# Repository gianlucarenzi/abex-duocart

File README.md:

Atari DUO Cart for ABEX
=====================

This is a Atari Duo Cart board, designed for the Atari PBI & ECI Bus EXtender
or ABEX for short.

This Atari DUO Cart is a derivated work of the famous Uno-Cart Project

Rendered Images
===============
# Front
# Back
# Overall

Hardware License
================
Copyright (C) 2018/2019 Gianluca Renzi <gianlucarenzi@eurek.it> <icjtqr@gmail.com>

The hardware of this project is released as free/open hardware under the
Creative Commons Attribution Share-Alike license. See `LICENSE.hw` for details.

Firmware License
================
Copyright (C) 2019 Gianluca Renzi <icjtqr@gmail.com>

The microcontroller firmware of this project is released as free software,
under the terms of the GNU General Public License v3, or later.  See
`LICENSE.sw` for details.

Software License
================
The host software (amigafloppy tool) is released as free software, under the
terms of the GNU General Public License v3, or later. See `LICENSE.sw` or licence.txt for
details.

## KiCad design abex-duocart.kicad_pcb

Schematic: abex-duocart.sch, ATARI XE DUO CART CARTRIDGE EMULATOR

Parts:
C30: 100n; C_1206_HandSoldering
FT232RPi.1: CONN_01X03; Pin_Header_Straight_1x03
JP1: CONN_01X02; Pin_Header_Straight_1x02
JP2: CONN_01X04; Pin_Header_Angled_1x04
P1: 0877159106; BUS_PCIexpress_64pin
P2, P3, P4, P5: CONN_01X01; MountingHole
R1: 0; R_1206_HandSoldering
R6: 100K; R_1206_HandSoldering
SW2: SW_Push; SW_SPST_FSMSM_3D

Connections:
GND: C30.1, FT232RPi.1.1, JP1.2, JP2.1, P1.A1, P1.A5, P1.A9, P1.A13, P1.A17, P1.A21, P1.A25, P1.A29, P1.A32, P1.B17, P1.B21, P1.B25, R1.2, SW2.1; also elsewhere on the board
SWDCLK: JP2.3, P1.B29; also elsewhere on the board
SWDIO: JP2.2, P1.B27; also elsewhere on the board
SWDRST: C30.2, JP1.1, P1.B31, R6.1, SW2.2; also elsewhere on the board
UART_RX: FT232RPi.1.2; also elsewhere on the board
UART_TX: FT232RPi.1.3; also elsewhere on the board
VCC_3V3: JP2.4, P1.A3, P1.A7, P1.A11, P1.A15, P1.A19, P1.A23, P1.A27, P1.B19, P1.B23, R6.2; also elsewhere on the board
mA0: P1.B32; also elsewhere on the board
mA1: P1.B30; also elsewhere on the board
mA2: P1.B28; also elsewhere on the board
mA3: P1.B26; also elsewhere on the board
mA4: P1.B24; also elsewhere on the board
mA5: P1.B22; also elsewhere on the board
mA6: P1.B20; also elsewhere on the board
mA7: P1.B18; also elsewhere on the board
mA8: P1.B16; also elsewhere on the board
mA9: P1.B14; also elsewhere on the board
mA10: P1.B12; also elsewhere on the board
mA11: P1.B10; also elsewhere on the board
mA12: P1.B8; also elsewhere on the board
mA13: P1.B6; also elsewhere on the board
mA14: P1.B4; also elsewhere on the board
mA15: P1.B2; also elsewhere on the board
mAUDIO: P1.A6, R1.1
mD0: P1.B15; also elsewhere on the board
mD1: P1.B13; also elsewhere on the board
mD2: P1.B11; also elsewhere on the board
mD3: P1.B9; also elsewhere on the board
mD4: P1.B7; also elsewhere on the board
mD5: P1.B5; also elsewhere on the board
mD6: P1.B3; also elsewhere on the board
mD7: P1.B1; also elsewhere on the board
mPHI2: P1.A4; also elsewhere on the board
mR/~W: P1.A10; also elsewhere on the board
mRD4: P1.A24; also elsewhere on the board
mRD5: P1.A28; also elsewhere on the board
~mCCTL: P1.A30; also elsewhere on the board
~mREF: P1.A8; also elsewhere on the board
~mRST: P1.A2; also elsewhere on the board
~mS4: P1.A22; also elsewhere on the board
~mS5: P1.A26; also elsewhere on the board

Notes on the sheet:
DEBUG/PROGRAMMING SECTION MEMORY
MOUNTING HOLES
RESET BUTTON MEM
DNP
ABEX PCI EXPRESS CARD CONNECTOR 64 PIN
A31 is +5VDC. Unused here

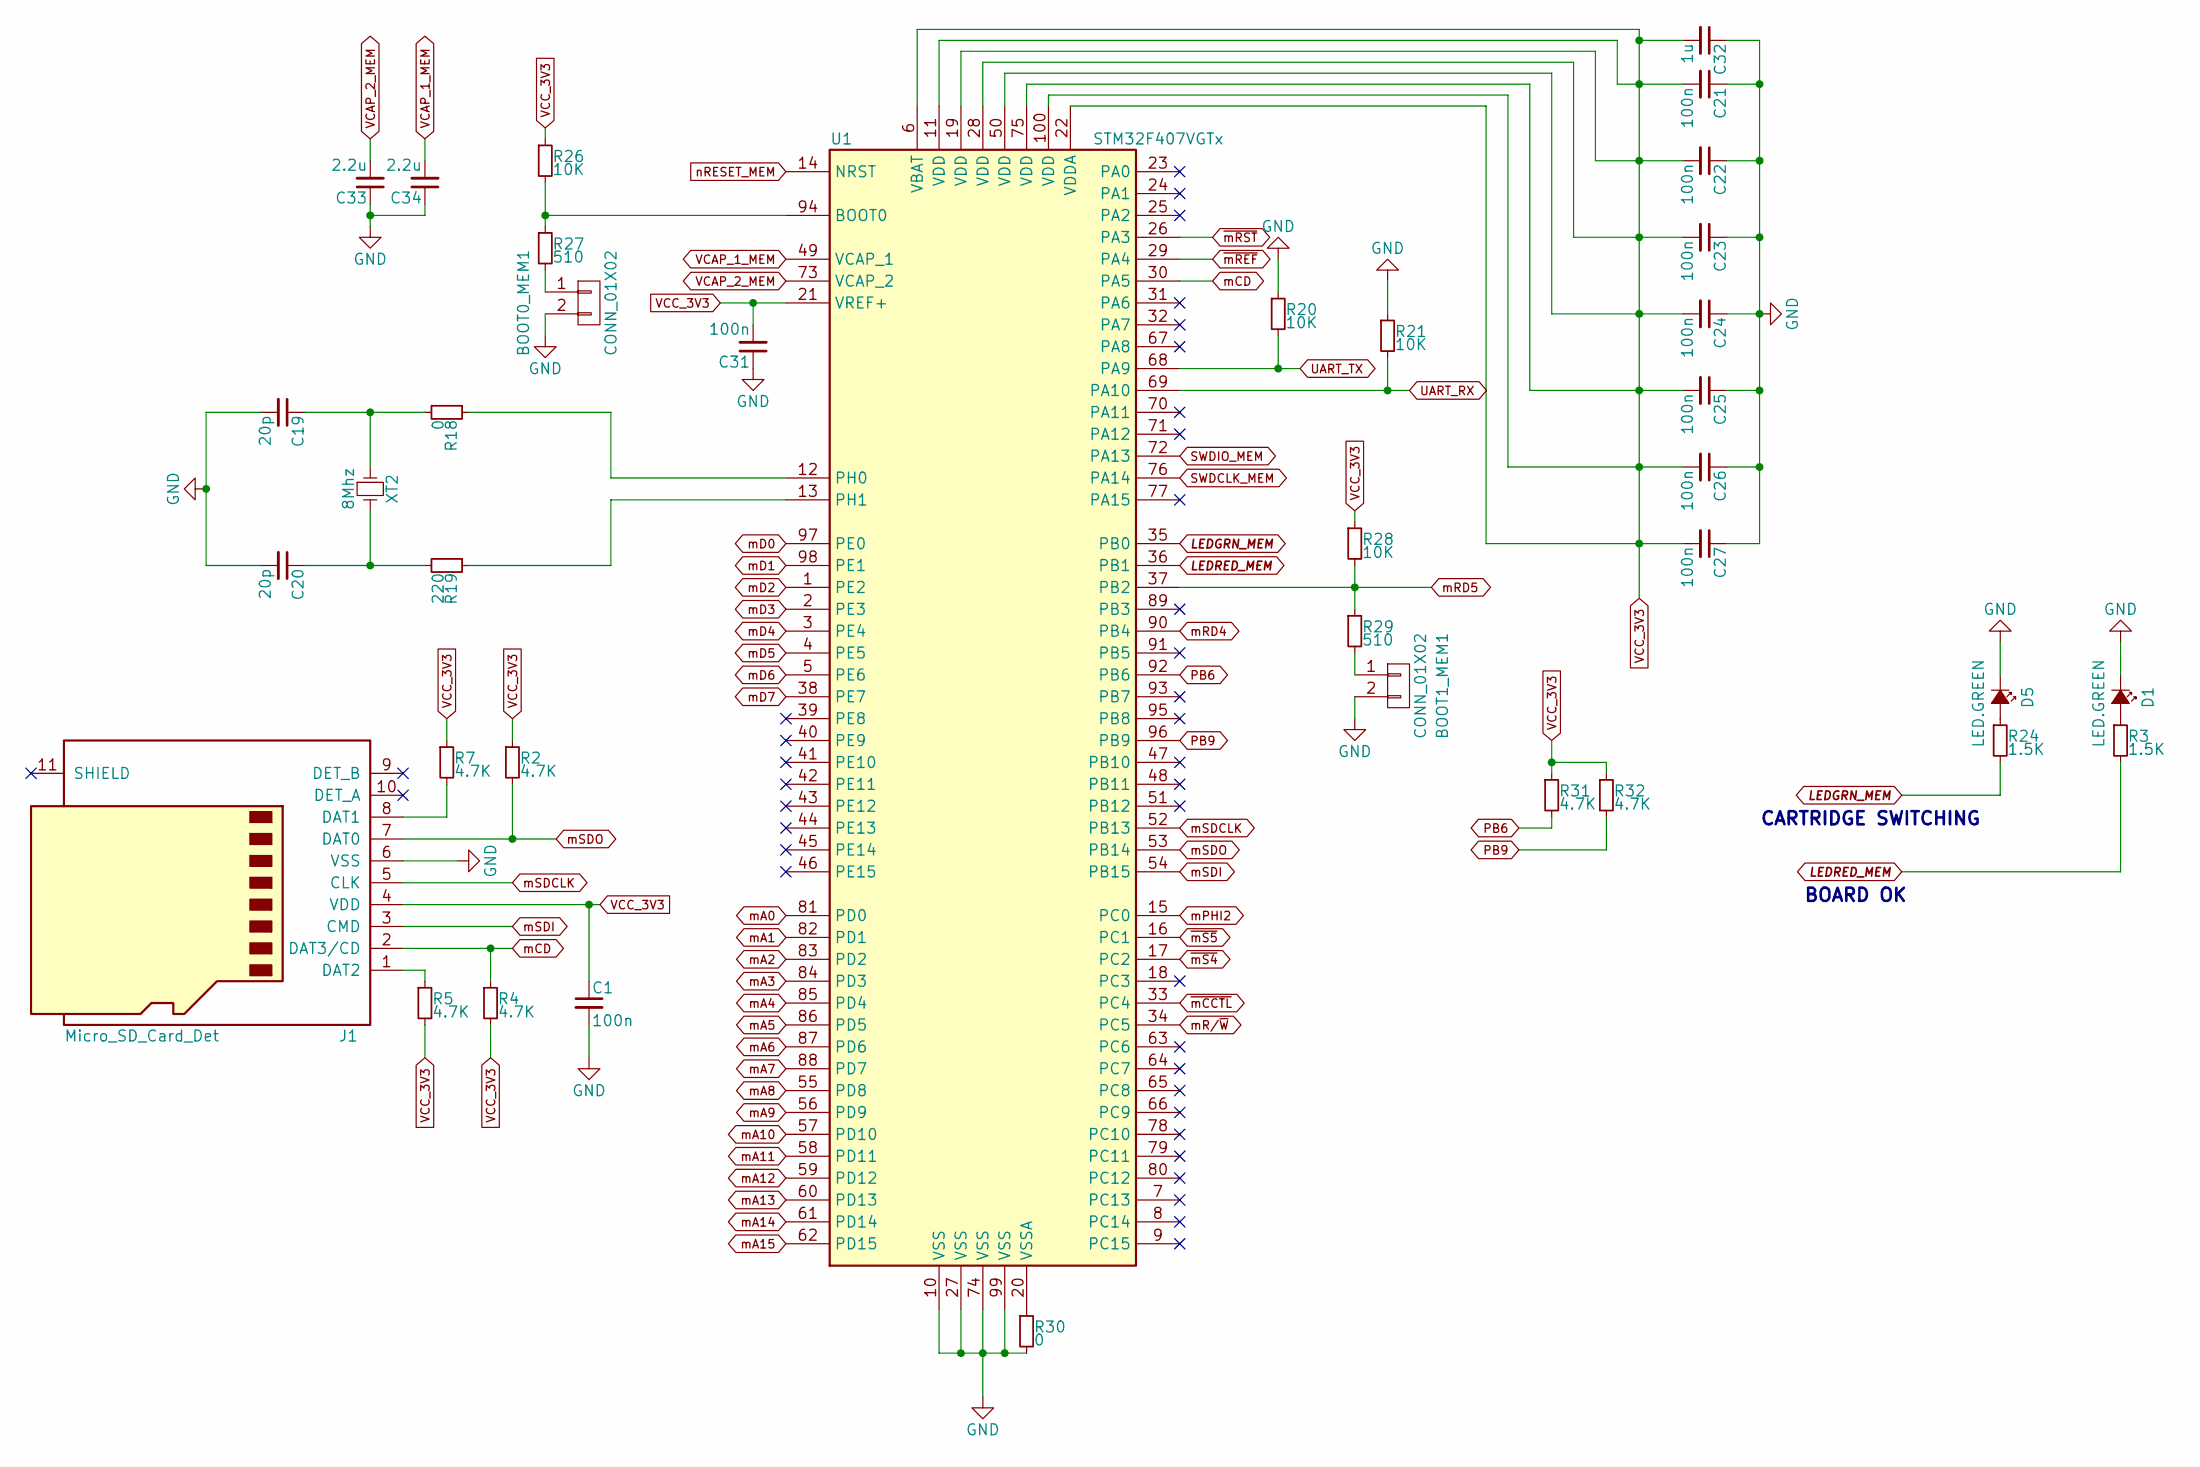
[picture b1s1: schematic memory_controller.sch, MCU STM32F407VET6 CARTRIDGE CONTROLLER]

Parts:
BOOT0_MEM1, BOOT1_MEM1: CONN_01X02; Pin_Header_Straight_1x02
C1, C21, C22, C23, C24, C25, C26, C27, C31: 100n; C_1206_HandSoldering
C19, C20: 20p; C_1206_HandSoldering
C32: 1u; C_1206_HandSoldering
C33, C34: 2.2u; C_1206_HandSoldering
D1, D5: LED.GREEN; LED_1206
J1: Micro_SD_Card_Det; microSD_HC_Hirose_DM3D-SF
R2, R4, R5, R7, R31, R32: 4.7K; R_1206_HandSoldering
R3, R24: 1.5K; R_1206_HandSoldering
R18, R30: 0; R_1206_HandSoldering
R19: 220; R_1206_HandSoldering
R20, R21, R26, R28: 10K; R_1206_HandSoldering
R27, R29: 510; R_1206_HandSoldering
U1: STM32F407VGTx; TQFP-100_14x14mm_Pitch0.5mm
XT2: 8Mhz; Crystal_HC49-4H_Vertical_3D

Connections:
GND: BOOT0_MEM1.2, BOOT1_MEM1.2, C1.2, C19.2, C20.2, C21.1, C22.1, C23.1, C24.1, C25.1, C26.1, C27.1, C31.1, C32.1, C33.1, C34.1, D1.1 (K), D5.1 (K), J1.6 (VSS), R20.1, R21.1, R30.2, U1.10 (VSS), U1.27 (VSS), U1.74 (VSS), U1.99 (VSS); also elsewhere on the board
LEDGRN_MEM: R24.2, U1.35 (PB0)
LEDRED_MEM: R3.2, U1.36 (PB1)
unnamed: BOOT0_MEM1.1, R27.2
unnamed: BOOT1_MEM1.1, R29.2
unnamed: C19.1, R18.2, XT2.1
unnamed: C20.1, R19.2, XT2.2
unnamed: D1.2 (A), R3.1
unnamed: D5.2 (A), R24.1
unnamed: J1.1 (DAT2), R5.1
unnamed: J1.8 (DAT1), R7.2
unnamed: R18.1, U1.12 (PH0)
unnamed: R19.1, U1.13 (PH1)
unnamed: R26.2, R27.1, U1.94 (BOOT0)
unnamed: R30.1, U1.20 (VSSA)
PB6: R31.2, U1.92 (PB6)
PB9: R32.2, U1.96 (PB9)
SWDCLK: U1.76 (PA14); also elsewhere on the board
SWDIO: U1.72 (PA13); also elsewhere on the board
SWDRST: U1.14 (NRST); also elsewhere on the board
UART_RX: R21.2, U1.69 (PA10); also elsewhere on the board
UART_TX: R20.2, U1.68 (PA9); also elsewhere on the board
VCAP_1_MEM: C34.2, U1.49 (VCAP_1)
VCAP_2_MEM: C33.2, U1.73 (VCAP_2)
VCC_3V3: C1.1, C21.2, C22.2, C23.2, C24.2, C25.2, C26.2, C27.2, C31.2, C32.2, J1.4 (VDD), R2.1, R4.2, R5.2, R7.1, R26.1, R28.1, R31.1, R32.1, U1.6 (VBAT), U1.11 (VDD), U1.19 (VDD), U1.21 (VREF+), U1.22 (VDDA), U1.28 (VDD), U1.50 (VDD), U1.75 (VDD), U1.100 (VDD); also elsewhere on the board
mA0: U1.81 (PD0); also elsewhere on the board
mA1: U1.82 (PD1); also elsewhere on the board
mA2: U1.83 (PD2); also elsewhere on the board
mA3: U1.84 (PD3); also elsewhere on the board
mA4: U1.85 (PD4); also elsewhere on the board
mA5: U1.86 (PD5); also elsewhere on the board
mA6: U1.87 (PD6); also elsewhere on the board
mA7: U1.88 (PD7); also elsewhere on the board
mA8: U1.55 (PD8); also elsewhere on the board
mA9: U1.56 (PD9); also elsewhere on the board
mA10: U1.57 (PD10); also elsewhere on the board
mA11: U1.58 (PD11); also elsewhere on the board
mA12: U1.59 (PD12); also elsewhere on the board
mA13: U1.60 (PD13); also elsewhere on the board
mA14: U1.61 (PD14); also elsewhere on the board
mA15: U1.62 (PD15); also elsewhere on the board
mCD: J1.2 (DAT3/CD), R4.1, U1.30 (PA5)
mD0: U1.97 (PE0); also elsewhere on the board
mD1: U1.98 (PE1); also elsewhere on the board
mD2: U1.1 (PE2); also elsewhere on the board
mD3: U1.2 (PE3); also elsewhere on the board
mD4: U1.3 (PE4); also elsewhere on the board
mD5: U1.4 (PE5); also elsewhere on the board
mD6: U1.5 (PE6); also elsewhere on the board
mD7: U1.38 (PE7); also elsewhere on the board
mPHI2: U1.15 (PC0); also elsewhere on the board
mR/~W: U1.34 (PC5); also elsewhere on the board
mRD4: U1.90 (PB4); also elsewhere on the board
mRD5: R28.2, R29.1, U1.37 (PB2); also elsewhere on the board
mSDCLK: J1.5 (CLK), U1.52 (PB13)
mSDI: J1.3 (CMD), U1.54 (PB15)
mSDO: J1.7 (DAT0), R2.2, U1.53 (PB14)
~mCCTL: U1.33 (PC4); also elsewhere on the board
~mREF: U1.29 (PA4); also elsewhere on the board
~mRST: U1.26 (PA3); also elsewhere on the board
~mS4: U1.17 (PC2); also elsewhere on the board
~mS5: U1.16 (PC1); also elsewhere on the board

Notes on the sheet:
CARTRIDGE SWITCHING
BOARD OK

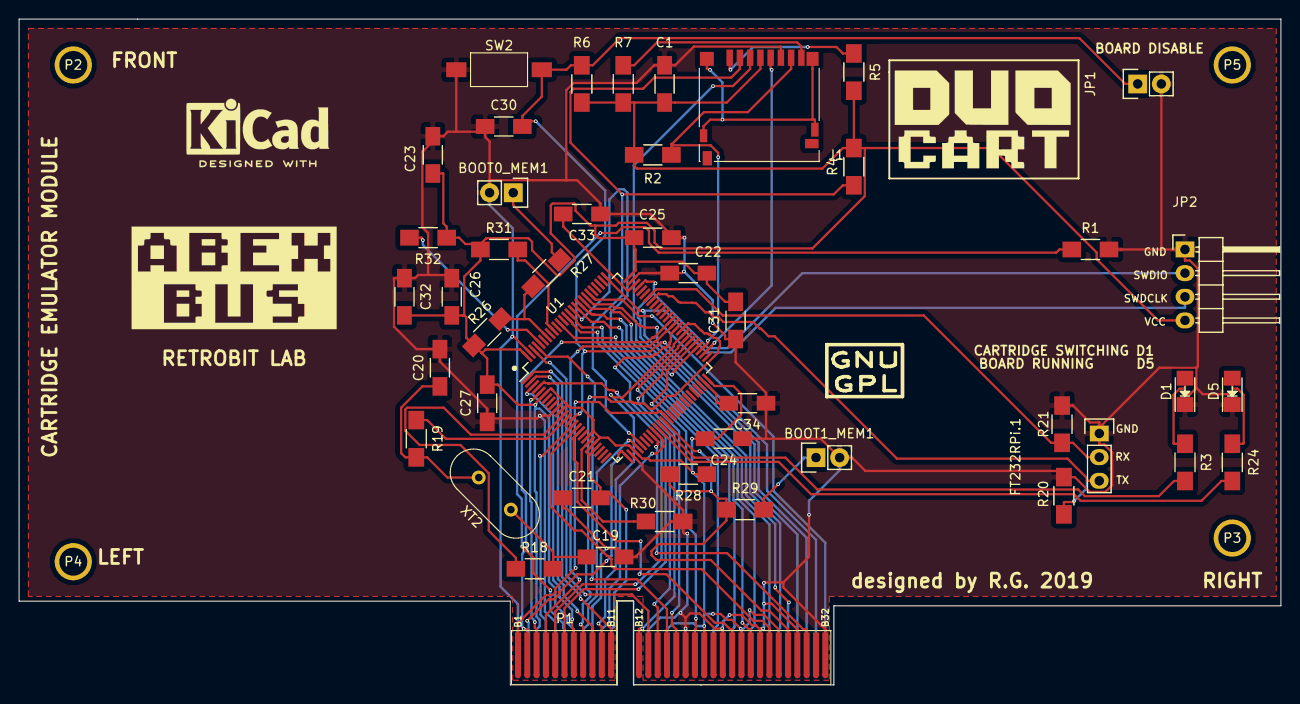
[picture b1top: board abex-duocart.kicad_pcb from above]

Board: 2 copper layers, 135.5 x 71.5 mm, 54 parts (0 on the bottom side), 63 nets.

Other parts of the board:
ATARI800XL: LOGO; ABEX_Logo_22mmx11mm_WB
DUOCART: LOGO; DUOCart_20x11_Rev
GPL: Symbol_GNU-GPL_CopperTop_Small; Symbol_GNU-GPL_SilkScreen_Small
KICAD: KiCad-Logo2_6mm_SilkScreen

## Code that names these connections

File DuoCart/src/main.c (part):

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
GPIO_InitTypeDef  GPIO_InitStructure;

/* Green LED -> PB0, Red LED -> PB1, RD5 -> PB2, RD4 -> PB4 */
static void config_gpio_leds_RD45()
{
	/* GPIOB Periph clock enable */
	RCC_AHB1PeriphClockCmd(RCC_AHB1Periph_GPIOB, ENABLE);
	/* Configure PB0, PB1in output pushpull mode */
	GPIO_InitStructure.GPIO_Pin = GPIO_Pin_0 | GPIO_Pin_1 | GPIO_Pin_2 | GPIO_Pin_4;
	GPIO_InitStructure.GPIO_Mode = GPIO_Mode_OUT;
	GPIO_InitStructure.GPIO_OType = GPIO_OType_PP;
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}

/* Input Signals GPIO pins on:
 *  CLK -> PC0, /S5 -> PC1, /S4 ->PC2,  TP1 -> PC3, CCTL -> PC4, R/W -> PC5
 */
static void config_gpio_sig(void)
{
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	// Enable clock for USART1
	RCC_APB2PeriphClockCmd(RCC_APB2Periph_USART1, ENABLE);

	// Connect PA9 to USART1_Tx
	GPIO_PinAFConfig(DEBUG_PORT, DEBUG_PINSRC_TX, GPIO_AF_USART1);
	// Connect PA10 to USART1_Rx
	GPIO_PinAFConfig(DEBUG_PORT, DEBUG_PINSRC_RX, GPIO_AF_USART1);

	// Initialization of DEBUG UART GPIO
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
	DBG_V("ATARI COMPUTER IN RESET MODE\r\n");

	/* Ouptut: LEDS - PB{0..1}, RD5 - PB2, RD4 - PB4 */
	config_gpio_leds_RD45();
	/* InOut: Data - PE{8..15} */
	config_gpio_data();
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
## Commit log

2019-06-02 Corrected some silkscreen bugs
2019-06-27 Added for debug purposes
2019-06-27 Added DEBUG flags
2019-06-27 Add optimization flag for march=armv7e-m
2019-06-27 Add Optimization level and USART support
2019-06-27 Optimized. Drop other old stuff. No more shifting when reading from DATABUS. It will be faster now
2019-06-27 Added the CardDetect. Added the A31 +5V pin
2019-06-28 Configured PULLUP for Data Lines
2019-06-28 Added spaces and improved readabilty of the code
2025-11-01 RetroBitLab library

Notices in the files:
DuoCart/src/main.c:
DUOCart Firmware (c)2019 Gianluca Renzi
based on the original work by:
UNOCart Firmware (c)2016 Robin Edwards
